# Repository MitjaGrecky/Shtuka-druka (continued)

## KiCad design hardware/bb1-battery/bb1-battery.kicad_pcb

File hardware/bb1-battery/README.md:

# BB1 - battery board (rev 0.4, 25.11.2026; P143, P144, P146, P150, P155)

One long board, **398 x 28 mm, 2 layers, 2 oz copper, 70 parts, 58 nets**, along the ends of the three cell blocks under the pads (model x 104-502, y 156-184, z 3-14; 3 mm standoffs). It replaces the BM boards 38 x 38 mm.
**Schematic and placed board; not routed** (`UNROUTED`). ERC 0, DRC 0 errors, parity 0. Positions: `model3d/batt_bays/under_pads.csv` (P144); board x = model x - 104, y = model y - 156.

| Block | Parts | Notes |
|---|---|---|
| 6 cells | **solder pads** for the two wires of each Ampul cell (WirePads_2x_THT: 4.2 mm pads, 1.6 mm holes, 8 mm pitch, two 3 mm holes for a cable tie), pad 1 +, pad 2 - | x 52.5, 77.5, 186.5, 211.5, 320.5, 345.5 (block centres 65, 199, 333 +- 12.5; y 7); >= 1.0 mm2 wire, 8 A per cell track (>= 3 mm at 2 oz, P155); pack A = blocks 1, 2, 3 first cells in series, pack B the second cells; no power connectors (P146) |
| 2 protections | BQ7791500 + 2 x CSD18532Q5B + 5 mOhm + balancing, the circuit of `bm-bms3s` (25 parts each, nets suffixed _A / _B) | between the cell connectors (x 112 and 266): OV 4.2 V, UV 2.9 V, OCD 12 A, OTC 45 C |
| 2 outputs to PW | Micro-Fit 43045-0600 2x3 (C127367), J7 pack A, J8 pack B | BAT+ x 2, GND x 2, NTC, GND = PW Battery 1 / 2; x 150 and 250 |
| 4 NTC sockets | JST GH-class 1.25 mm latching, 2 pins (BM02B-GHS-TBT footprint; series by the technologist), 103AT 10k | J9 chip A, J10 chip B (TS), J11, J12 for the chargers of PW (separate thermistors) |
| 8 mounting holes | M3 | assumed: ends and ribs (x 4, 132, 266, 394, on the ribs); the csv has no holes |

**Order requirement: 2 oz copper (70 um) on both layers is mandatory** (state it in the fab order; 1 oz is not acceptable). Power tracks >= 3 mm, 8 A per cell/pack path.

8 A (1C of an 8 Ah cell): tracks on 2 oz copper **>= 3 mm** (IPC-2152) at routing; the 4 nets of each pack and PACK_N run the length of the board, use both layers.
Open: the 4th NTC (the order said 3), holes with the designer, GH or ZH series (technologist), routing. License: CERN-OHL-S-2.0, AGPL-3.0-or-later.

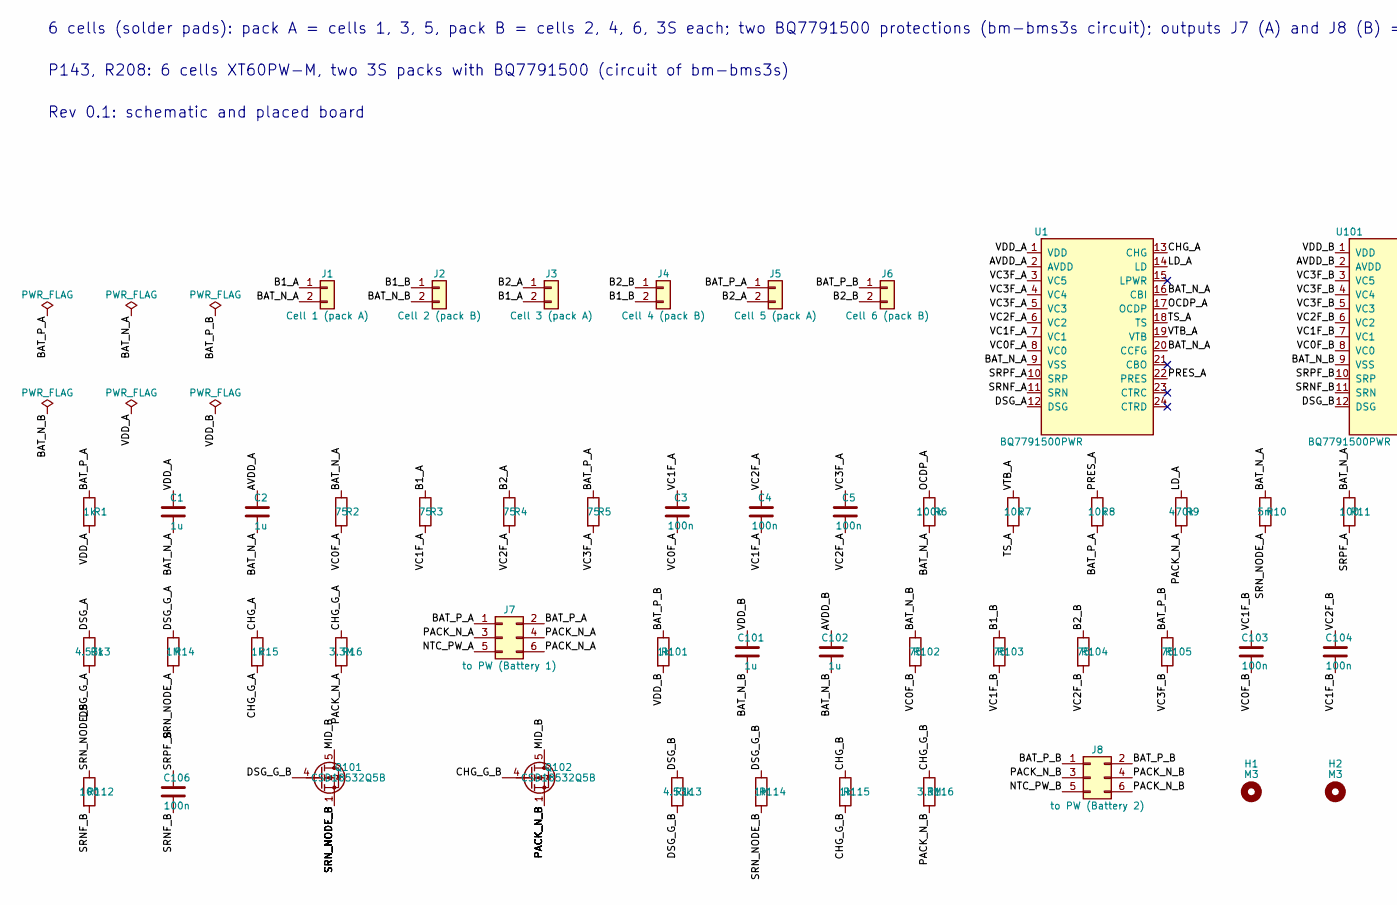
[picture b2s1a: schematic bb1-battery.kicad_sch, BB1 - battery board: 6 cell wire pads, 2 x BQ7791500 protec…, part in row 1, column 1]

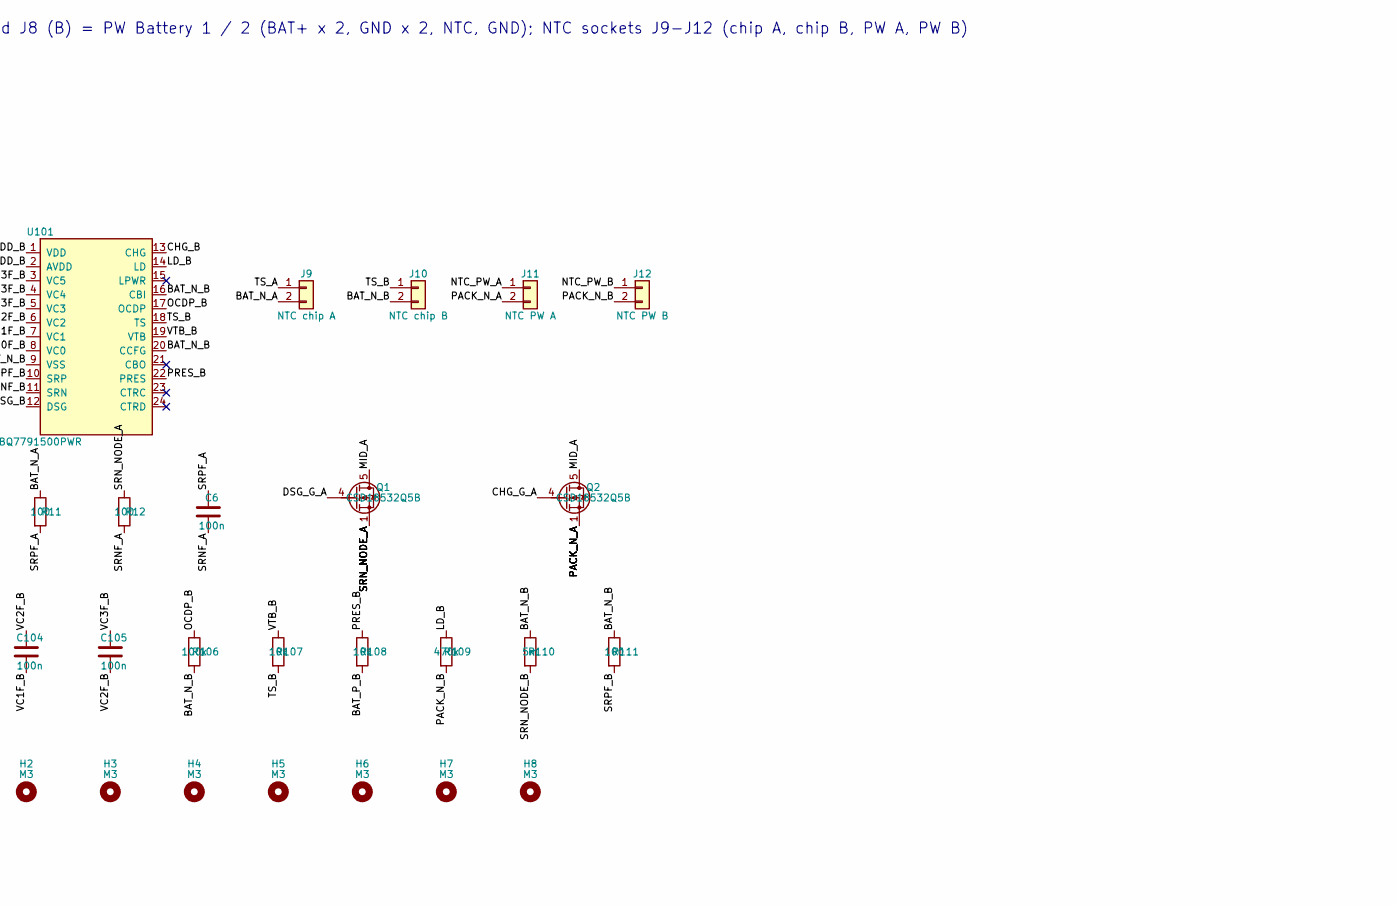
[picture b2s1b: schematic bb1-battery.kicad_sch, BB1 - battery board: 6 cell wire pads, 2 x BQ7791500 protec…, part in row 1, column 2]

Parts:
C1, C2, C101, C102: 1u; C_0603_1608Metric; LCSC C52923
C3, C4, C5, C6, C103, C104, C105, C106: 100n; C_0402_1005Metric; LCSC C1525
H1, H2, H3, H4, H5, H6, H7, H8: M3; MountingHole_3.2mm_M3_ISO7380
J1: Cell 1 (pack A); WirePads_2x_THT_P8.0mm_TieHoles
J2: Cell 2 (pack B); WirePads_2x_THT_P8.0mm_TieHoles
J3: Cell 3 (pack A); WirePads_2x_THT_P8.0mm_TieHoles
J4: Cell 4 (pack B); WirePads_2x_THT_P8.0mm_TieHoles
J5: Cell 5 (pack A); WirePads_2x_THT_P8.0mm_TieHoles
J6: Cell 6 (pack B); WirePads_2x_THT_P8.0mm_TieHoles
J7: to PW (Battery 1); Molex_Micro-Fit_3.0_43045-0600_2x03_P3.00mm_Horizontal; LCSC C127367
J8: to PW (Battery 2); Molex_Micro-Fit_3.0_43045-0600_2x03_P3.00mm_Horizontal; LCSC C127367
J9: NTC chip A; JST_GH_BM02B-GHS-TBT_1x02-1MP_P1.25mm_Vertical
J10: NTC chip B; JST_GH_BM02B-GHS-TBT_1x02-1MP_P1.25mm_Vertical
J11: NTC PW A; JST_GH_BM02B-GHS-TBT_1x02-1MP_P1.25mm_Vertical
J12: NTC PW B; JST_GH_BM02B-GHS-TBT_1x02-1MP_P1.25mm_Vertical
Q1, Q2, Q101, Q102: CSD18532Q5B; TDSON-8-1; LCSC C882766
R1, R15, R101, R115: 1k; R_0402_1005Metric; LCSC C11702
R2, R3, R4, R5, R102, R103, R104, R105: 75; R_0402_1005Metric; LCSC C114757
R6, R106: 100k; R_0402_1005Metric; LCSC C25741
R7, R8, R107, R108: 10k; R_0402_1005Metric; LCSC C25744
R9, R109: 470k; R_0402_1005Metric; LCSC C25790
R10, R110: 5m; R_2512_6332Metric; LCSC C2903482
R11, R12, R111, R112: 100; R_0402_1005Metric; LCSC C25076
R13, R113: 4.53k; R_0402_1005Metric; LCSC C79537
R14, R114: 1M; R_0402_1005Metric; LCSC C26083
R16, R116: 3.3M; R_0402_1005Metric; LCSC C270613
U1, U101: BQ7791500PWR; TSSOP-24_4.4x7.8mm_P0.65mm; LCSC C2876946

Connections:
/AVDD_A: C2.1, U1.2 (AVDD)
/AVDD_B: C102.1, U101.2 (AVDD)
/B1_A: J1.1, J3.2, R3.1
/B1_B: J2.1, J4.2, R103.1
/B2_A: J3.1, J5.2, R4.1
/B2_B: J4.1, J6.2, R104.1
/BAT_N_A: C1.2, C2.2, J1.2, J9.2, R2.1, R6.2, R10.1, R11.1, U1.9 (VSS), U1.16 (CBI), U1.20 (CCFG)
/BAT_N_B: C101.2, C102.2, J2.2, J10.2, R102.1, R106.2, R110.1, R111.1, U101.9 (VSS), U101.16 (CBI), U101.20 (CCFG)
/BAT_P_A: J5.1, J7.1, J7.2, R1.1, R5.1, R8.2
/BAT_P_B: J6.1, J8.1, J8.2, R101.1, R105.1, R108.2
/CHG_A: R15.1, U1.13 (CHG)
/CHG_B: R115.1, U101.13 (CHG)
/CHG_G_A: Q2.4 (G), R15.2, R16.1
/CHG_G_B: Q102.4 (G), R115.2, R116.1
/DSG_A: R13.1, U1.12 (DSG)
/DSG_B: R113.1, U101.12 (DSG)
/DSG_G_A: Q1.4 (G), R13.2, R14.1
/DSG_G_B: Q101.4 (G), R113.2, R114.1
/LD_A: R9.1, U1.14 (LD)
/LD_B: R109.1, U101.14 (LD)
/MID_A: Q1.5 (D), Q2.5 (D)
/MID_B: Q101.5 (D), Q102.5 (D)
/NTC_PW_A: J7.5, J11.1
/NTC_PW_B: J8.5, J12.1
/OCDP_A: R6.1, U1.17 (OCDP)
/OCDP_B: R106.1, U101.17 (OCDP)
/PACK_N_A: J7.3, J7.4, J7.6, J11.2, Q2.1 (S), Q2.2 (S), Q2.3 (S), R9.2, R16.2
/PACK_N_B: J8.3, J8.4, J8.6, J12.2, Q102.1 (S), Q102.2 (S), Q102.3 (S), R109.2, R116.2
/PRES_A: R8.1, U1.22 (PRES)
/PRES_B: R108.1, U101.22 (PRES)
/SRNF_A: C6.2, R12.2, U1.11 (SRN)
/SRNF_B: C106.2, R112.2, U101.11 (SRN)
/SRN_NODE_A: Q1.1 (S), Q1.2 (S), Q1.3 (S), R10.2, R12.1, R14.2
/SRN_NODE_B: Q101.1 (S), Q101.2 (S), Q101.3 (S), R110.2, R112.1, R114.2
/SRPF_A: C6.1, R11.2, U1.10 (SRP)
/SRPF_B: C106.1, R111.2, U101.10 (SRP)
/TS_A: J9.1, R7.2, U1.18 (TS)
/TS_B: J10.1, R107.2, U101.18 (TS)
/VC0F_A: C3.2, R2.2, U1.8 (VC0)
/VC0F_B: C103.2, R102.2, U101.8 (VC0)
/VC1F_A: C3.1, C4.2, R3.2, U1.7 (VC1)
/VC1F_B: C103.1, C104.2, R103.2, U101.7 (VC1)
/VC2F_A: C4.1, C5.2, R4.2, U1.6 (VC2)
/VC2F_B: C104.1, C105.2, R104.2, U101.6 (VC2)
/VC3F_A: C5.1, R5.2, U1.3 (VC5), U1.4 (VC4), U1.5 (VC3)
/VC3F_B: C105.1, R105.2, U101.3 (VC5), U101.4 (VC4), U101.5 (VC3)
/VDD_A: C1.1, R1.2, U1.1 (VDD)
/VDD_B: C101.1, R101.2, U101.1 (VDD)
/VTB_A: R7.1, U1.19 (VTB)
/VTB_B: R107.1, U101.19 (VTB)

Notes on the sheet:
6 cells (solder pads): pack A = cells 1, 3, 5, pack B = cells 2, 4, 6, 3S each; two BQ7791500 protections (bm-bms3s circuit); outputs J7 (A) and J8 (B) = PW Battery 1 / 2 (BAT+ x 2, GND x 2, NTC, GND); NTC sockets J9-J12 (chip A, chip B, PW A, PW B)
P143, R208: 6 cells XT60PW-M, two 3S packs with BQ7791500 (circuit of bm-bms3s)
Rev 0.1: schematic and placed board

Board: 2 copper layers, 70 parts (0 on the bottom side), 50 nets, no tracks yet.
